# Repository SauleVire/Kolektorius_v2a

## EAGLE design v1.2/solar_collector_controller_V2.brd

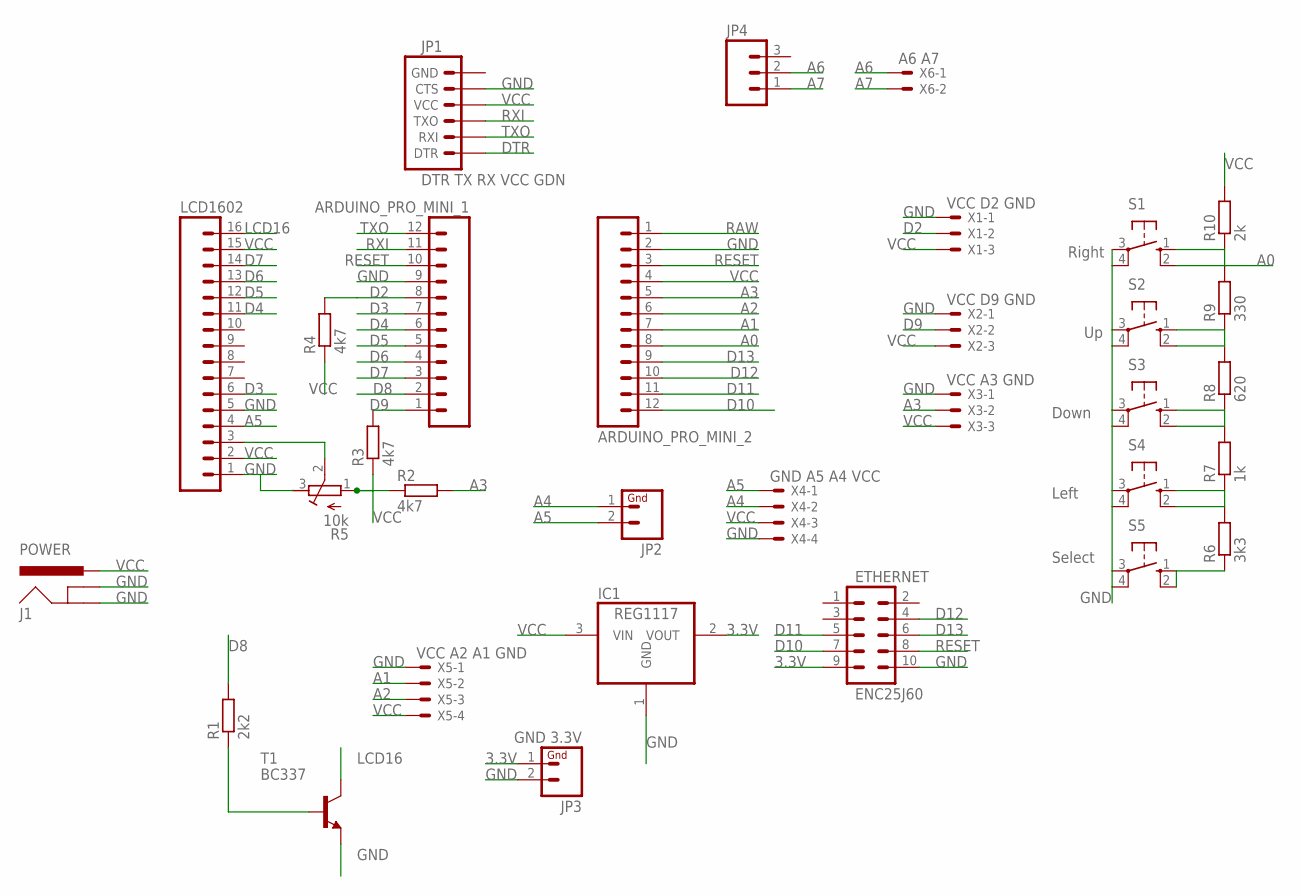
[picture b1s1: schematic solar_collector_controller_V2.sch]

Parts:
ARDUINO_PRO_MINI_1, ARDUINO_PRO_MINI_2: M12PTH; 1X12
ETHERNET: ENC25J60; AVR_ICSP
IC1: REG1117; SOT223
J1: POWER; POWER_JACK_PTH_LOCK
JP1: DTR TX RX VCC GDN; 1X06
JP2: M02PTH; 1X02
JP3: GND 3.3V; 1X02
JP4: M03PTH; 1X03
LCD1602: HEADER-16P-2.54; 16P-2.54
R1: 2k2; 0207/10
R2, R3, R4: 4k7; 0207/10
R5: 10k; RTRIM64W
R6: 3k3; 0207/10
R7: 1k; 0207/10
R8: 620; 0207/10
R9: 330; 0207/10
R10: 2k; 0207/10
S1: Right; B3F-10XX
S2: Up; B3F-10XX
S3: Down; B3F-10XX
S4: Left; B3F-10XX
S5: Select; B3F-10XX
T1: BC337; TO92
X1: VCC D2 GND; 22-23-2031
X2: VCC D9 GND; 22-23-2031
X3: VCC A3 GND; 22-23-2031
X4: GND A5 A4 VCC; 22-23-2041
X5: VCC A2 A1 GND; 22-23-2041
X6: A6 A7; 22-23-2021

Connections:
3.3V: ETHERNET.9, IC1.2 (VOUT), JP3.1
A0: ARDUINO_PRO_MINI_2.8, R9.2, R10.1, S1.1 (S), S1.2 (S1)
A1: ARDUINO_PRO_MINI_2.7, X5.2
A2: ARDUINO_PRO_MINI_2.6, X5.3
A3: ARDUINO_PRO_MINI_2.5, R2.2, X3.2
A4: JP2.1, X4.2
A5: JP2.2, LCD1602.4, X4.1
A6: JP4.2, X6.1
A7: JP4.1, X6.2
D2: ARDUINO_PRO_MINI_1.8, R4.2, X1.2
D3: ARDUINO_PRO_MINI_1.7, LCD1602.6
D4: ARDUINO_PRO_MINI_1.6, LCD1602.11
D5: ARDUINO_PRO_MINI_1.5, LCD1602.12
D6: ARDUINO_PRO_MINI_1.4, LCD1602.13
D7: ARDUINO_PRO_MINI_1.3, LCD1602.14
D8: ARDUINO_PRO_MINI_1.2, R1.2
D9: ARDUINO_PRO_MINI_1.1, R3.2, X2.2
D10: ARDUINO_PRO_MINI_2.12, ETHERNET.7
D11: ARDUINO_PRO_MINI_2.11, ETHERNET.5
D12: ARDUINO_PRO_MINI_2.10, ETHERNET.4
D13: ARDUINO_PRO_MINI_2.9, ETHERNET.6
DTR: JP1.1 (DTR)
GND: ARDUINO_PRO_MINI_1.9, ARDUINO_PRO_MINI_2.2, ETHERNET.10, IC1.1 (GND), J1.GND, J1.GNDBREAK, JP1.5 (CTS), JP3.2, LCD1602.1, LCD1602.5, R5.3 (A), S1.3, S1.4 (P1), S2.3, S2.4 (P1), S3.3, S3.4 (P1), S4.3, S4.4 (P1), S5.3, S5.4 (P1), T1.1 (E), X1.1, X2.1, X3.1, X4.4, X5.1
LCD16: LCD1602.16, T1.3 (C)
unnamed: LCD1602.3, R5.2 (S)
unnamed: R1.1, T1.2 (B)
unnamed: R6.1, S5.1 (S), S5.2 (S1)
unnamed: R6.2, R7.1, S4.1 (S), S4.2 (S1)
unnamed: R7.2, R8.1, S3.1 (S), S3.2 (S1)
unnamed: R8.2, R9.1, S2.1 (S), S2.2 (S1)
RAW: ARDUINO_PRO_MINI_2.1
RESET: ARDUINO_PRO_MINI_1.10, ARDUINO_PRO_MINI_2.3, ETHERNET.8
RXI: ARDUINO_PRO_MINI_1.11, JP1.3 (TXO)
TXO: ARDUINO_PRO_MINI_1.12, JP1.2 (RXI)
VCC: ARDUINO_PRO_MINI_2.4, IC1.3 (VIN), J1.PWR, JP1.4 (VCC), LCD1602.2, LCD1602.15, R2.1, R3.1, R4.1, R5.1 (E), R10.2, X1.3, X2.3, X3.3, X4.3, X5.4

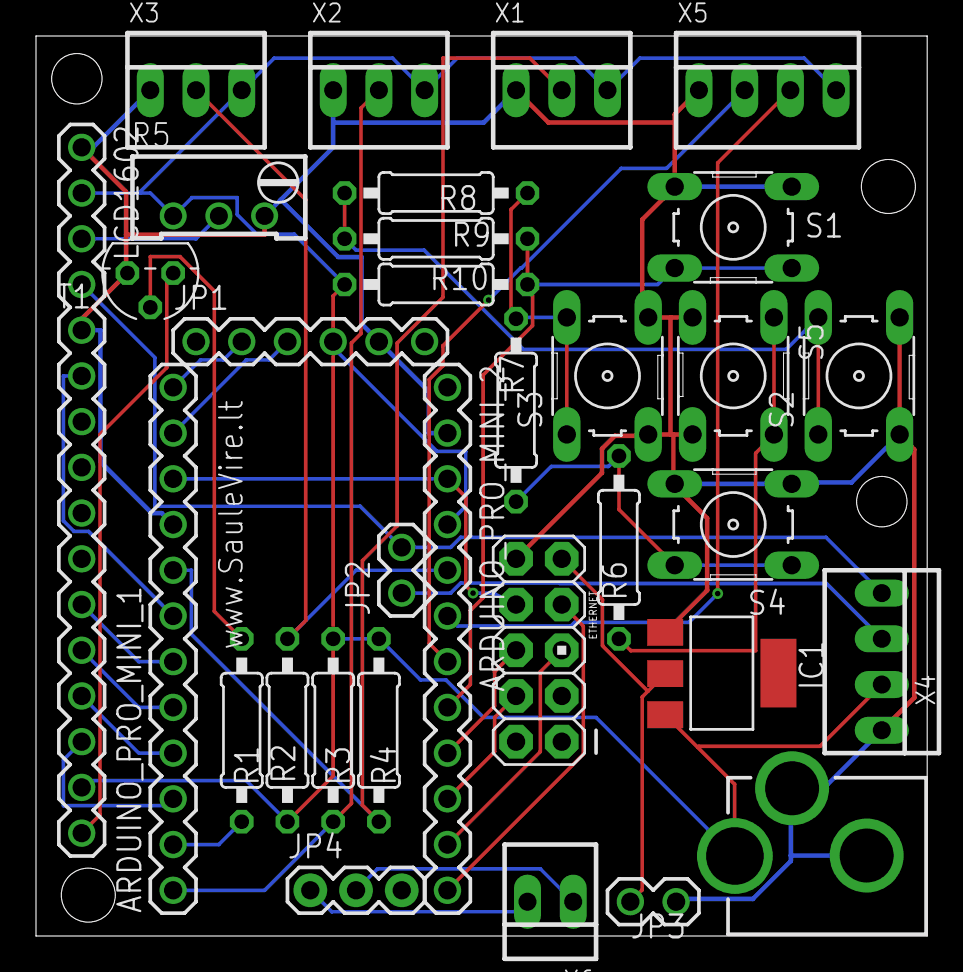
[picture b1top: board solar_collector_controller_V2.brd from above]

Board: 2 copper layers, 49.5 x 50.0 mm, 32 parts (0 on the bottom side), 33 nets.

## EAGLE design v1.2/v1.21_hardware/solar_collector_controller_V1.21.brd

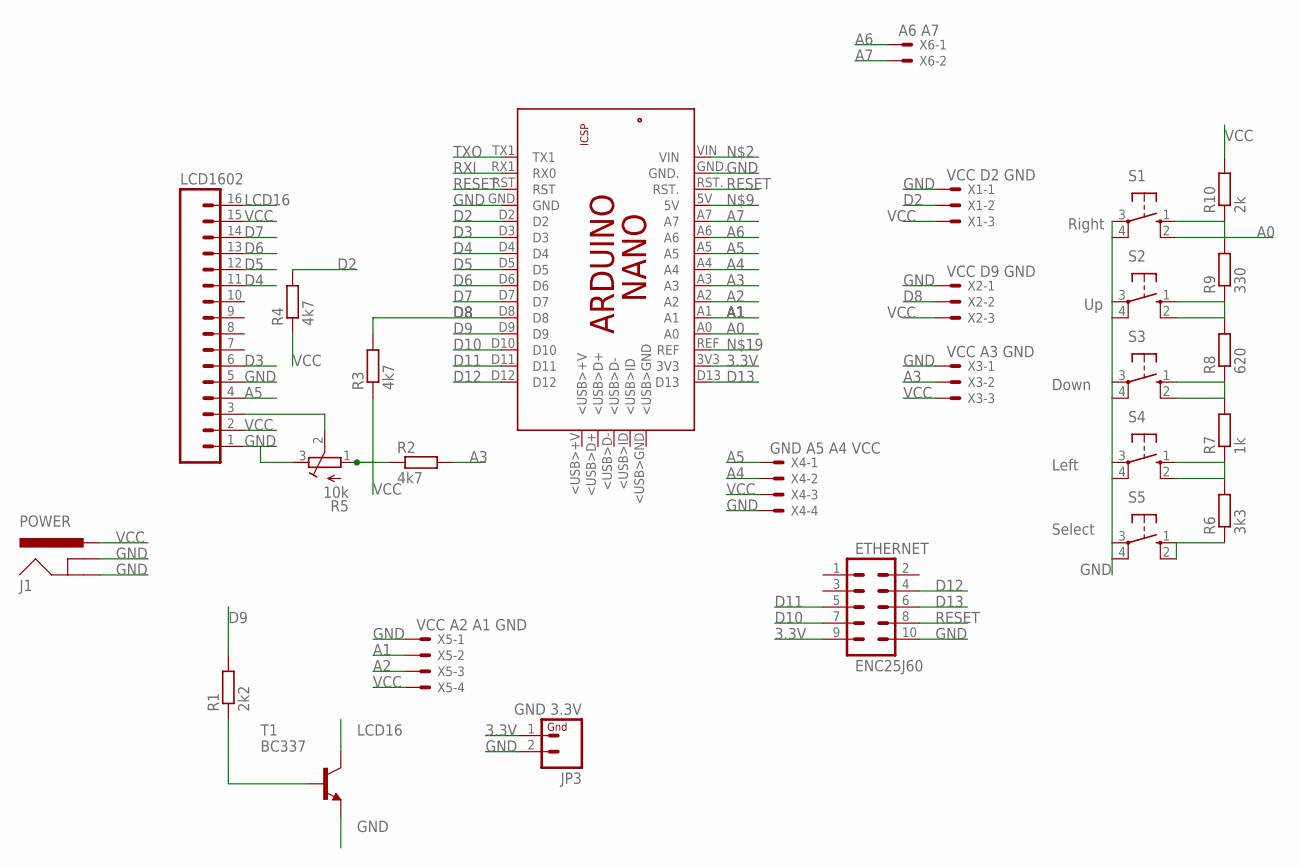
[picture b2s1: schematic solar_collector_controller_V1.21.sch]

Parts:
ETHERNET: ENC25J60; AVR_ICSP
J1: POWER; POWER_JACK_PTH_LOCK
JP3: GND 3.3V; 1X02
LCD1602: HEADER-16P-2.54; 16P-2.54
PCB1: ARDUINO_NANO
R1: 2k2; 0207/10
R2, R3, R4: 4k7; 0207/10
R5: 10k; RTRIM64W
R6: 3k3; 0207/10
R7: 1k; 0207/10
R8: 620; 0207/10
R9: 330; 0207/10
R10: 2k; 0207/10
S1: Right; B3F-10XX
S2: Up; B3F-10XX
S3: Down; B3F-10XX
S4: Left; B3F-10XX
S5: Select; B3F-10XX
T1: BC337; TO92
X1: VCC D2 GND; 22-23-2031
X2: VCC D9 GND; 22-23-2031
X3: VCC A3 GND; 22-23-2031
X4: GND A5 A4 VCC; 22-23-2041
X5: VCC A2 A1 GND; 22-23-2041
X6: A6 A7; 22-23-2021

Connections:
3.3V: ETHERNET.9, JP3.1, PCB1.3V3
A0: PCB1.A0, R9.2, R10.1, S1.1 (S), S1.2 (S1)
A1: PCB1.A1, X5.2
A2: PCB1.A2, X5.3
A3: PCB1.A3, R2.2, X3.2
A4: PCB1.A4, X4.2
A5: LCD1602.4, PCB1.A5, X4.1
A6: PCB1.A6, X6.1
A7: PCB1.A7, X6.2
D2: PCB1.D2, R4.2, X1.2
D3: LCD1602.6, PCB1.D3
D4: LCD1602.11, PCB1.D4
D5: LCD1602.12, PCB1.D5
D6: LCD1602.13, PCB1.D6
D7: LCD1602.14, PCB1.D7
D8: PCB1.D8, R3.2, X2.2
D9: PCB1.D9, R1.2
D10: ETHERNET.7, PCB1.D10
D11: ETHERNET.5, PCB1.D11
D12: ETHERNET.4, PCB1.D12
D13: ETHERNET.6, PCB1.D13
GND: ETHERNET.10, J1.GND, J1.GNDBREAK, JP3.2, LCD1602.1, LCD1602.5, PCB1.GND, PCB1.GND., R5.3 (A), S1.3, S1.4 (P1), S2.3, S2.4 (P1), S3.3, S3.4 (P1), S4.3, S4.4 (P1), S5.3, S5.4 (P1), T1.1 (E), X1.1, X2.1, X3.1, X4.4, X5.1
LCD16: LCD1602.16, T1.3 (C)
unnamed: LCD1602.3, R5.2 (S)
unnamed: R1.1, T1.2 (B)
unnamed: R6.1, S5.1 (S), S5.2 (S1)
unnamed: R6.2, R7.1, S4.1 (S), S4.2 (S1)
unnamed: R7.2, R8.1, S3.1 (S), S3.2 (S1)
unnamed: R8.2, R9.1, S2.1 (S), S2.2 (S1)
RESET: ETHERNET.8, PCB1.RST, PCB1.RST.
RXI: PCB1.RX1 (RX0)
TXO: PCB1.TX1
VCC: J1.PWR, LCD1602.2, LCD1602.15, R2.1, R3.1, R4.1, R5.1 (E), R10.2, X1.3, X2.3, X3.3, X4.3, X5.4

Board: 2 copper layers, 27 parts (0 on the bottom side), 31 nets, no tracks yet.

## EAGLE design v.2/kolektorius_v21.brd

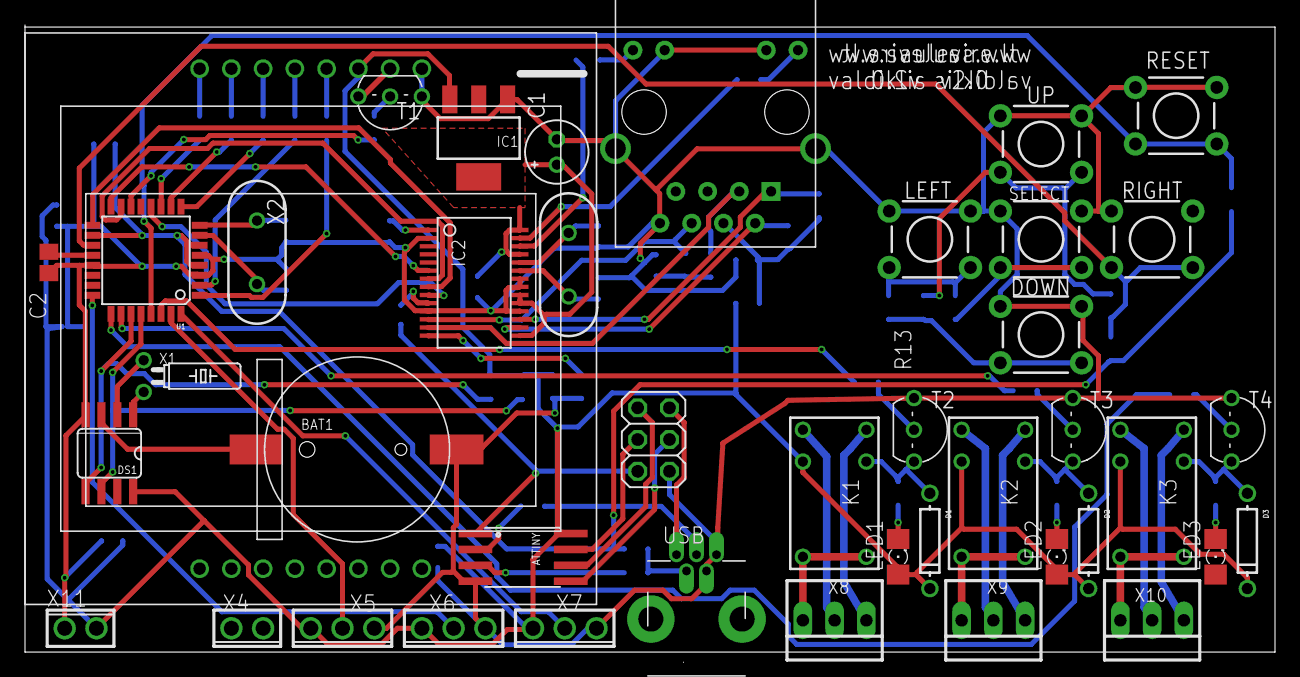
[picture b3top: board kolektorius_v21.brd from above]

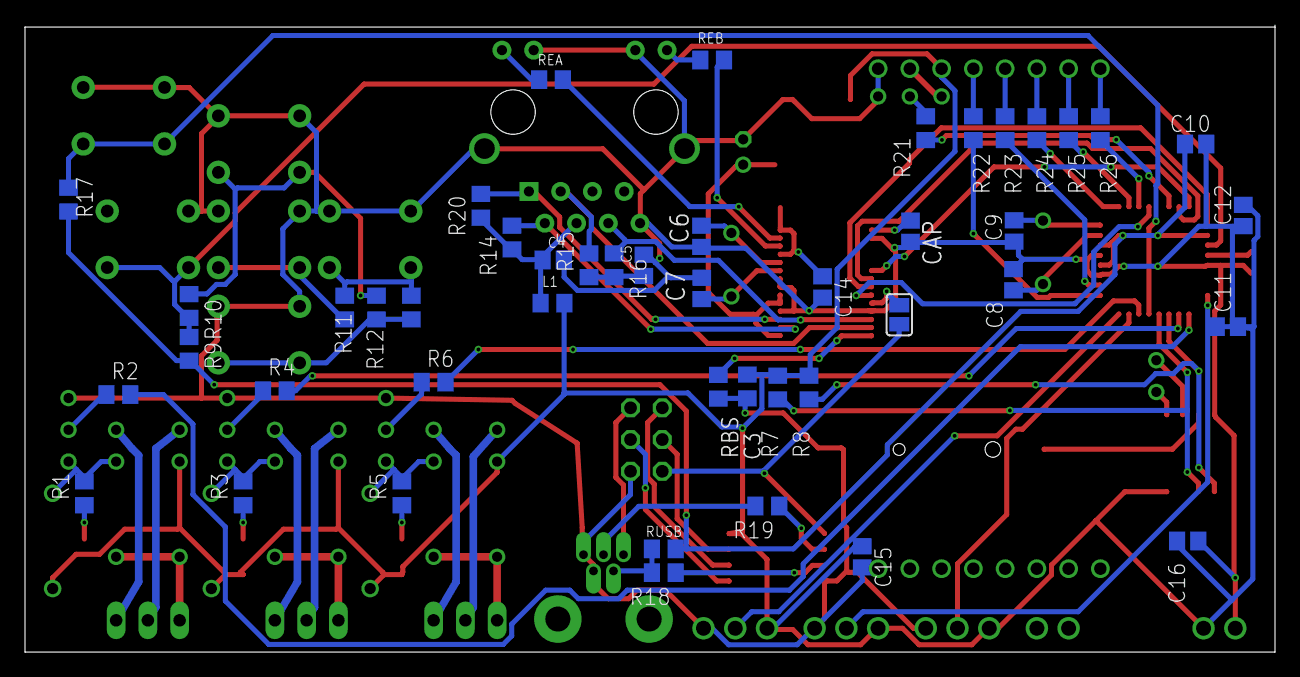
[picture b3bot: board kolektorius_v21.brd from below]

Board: 2 copper layers, 100.0 x 50.2 mm, 88 parts (46 on the bottom side), 83 nets.

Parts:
ATTINY: ATTINY45SO8S2; SO8S2
BAT1: BATTCON_12MM_SMT
C1: 100u; E2-5
C2, C10, C11, C12, C14, C15, C16: 100n; C0805
C3: 0.1u; C0805
C4, C5: 0.1µ; C0805
C6, C7: 18p; C0805
C8, C9: 22p; C0805
CAP: 10u; C0805
D1, D2, D3: DO-1N4148
DOWN: TACTILE-PTH
DS1: DS1307; SO08
IC1: LM1117-33; SOT223
IC2: ENC28J60; SSOP28DB
ISP: 2X03
K1, K2, K3: G5V1
L1: Bead; R0805
LED1, LED2, LED3: 1206
LEFT: TACTILE-PTH
R1, R3, R5: 470; R0805
R2, R4, R6, R11: 3k3; R0805
R7, R8, R17, R22, R23, R24, R25, R26: 10k; R0805
R9: 2k; R0805
R10: 330; R0805
R12: 620; R0805
R13, R21: 1k; R0805
R14, R15, R16, R20: 49; R0805
R18, R19: 47; R0805
RBS: 2.32K; R0805
REA: 330; R0805
REB: 330; R0805
RESET: TACTILE-PTH
RIGHT: TACTILE-PTH
RJ1: HR911105A
RUSB: 1.5k; R0805
SELECT: TACTILE-PTH
SJ1: SJ
T1, T2, T3, T4: 2N2222; TO92-EBC-OVAL
U1: ATMEGA328P; TQFP32-08
U$1: CELLPHONE_NOKIA_5100; CELLPHONE_NOKIA_5100_SPARKFUN
UP: TACTILE-PTH
USB: USB-MINIB-THM-MOLEX
X1: 32.768kHz; TC26H
X2: 16MHz; HC49US
X3: 25MHz; HC49US
X4, X11: 2POL254
X5, X6, X7: 3POL254
X8, X9, X10: 22-23-2031

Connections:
+3V3: C1.+, C14.1, IC1.4, IC2.15, IC2.19, IC2.20, IC2.25, IC2.28
+5V: ATTINY.8, C3.1, C11.2, C12.2, C15.1, C16.1, D1.C, D2.C, D3.C, DS1.8, IC1.3, K1.2, K2.2, K3.2, L1.2, LED1.A, LED2.A, R7.2, R8.2, U$1.P$6, X5.3, X6.3, X7.3, X11.2
A1: U1.24, X6.2
A2: R2.2, U1.25
A3: R4.2, U1.26
A6: R9.1, R10.2, RIGHT.3, RIGHT.4, U1.19
D0: R6.2, U1.30
D1: U1.31, X5.2
D2: U1.32, X7.2
D3: R22.2, U1.1
D4: R23.2, U1.2
D5: R24.2, U1.9
D6: R25.2, U1.10
D7: R26.2, U1.11
D8: IC2.9, U1.12
D10: R21.2, U1.14
D11: IC2.7, U1.15
D12: IC2.6, U1.16
D13: IC2.8, U1.17
D+: ATTINY.2, R19.1
D-: ATTINY.3, R18.1
GND: ATTINY.4, BAT1.P$1, C1.-, C2.2, C3.2, C4.1, C5.1, C6.2, C7.2, C8.1, C9.1, C10.2, C11.1, C12.1, C14.2, C15.2, C16.2, CAP.2, DOWN.1, DOWN.2, DS1.4, IC1.1, IC2.2, IC2.11, IC2.18, IC2.21, IC2.22, ISP.6, LEFT.1, LEFT.2, RBS.1, RESET.1, RESET.2, RIGHT.1, RJ1.G-, RJ1.GND, RJ1.SHIELD0, RJ1.SHIELD1, RJ1.Y-, SELECT.1, SELECT.2, T1.E, T2.E, T3.E, T4.E, U1.3, U1.5, U1.21, U$1.P$8, UP.1, UP.2, USB.GND, USB.ID, X5.1, X6.1, X7.1, X11.1
LEDA: REA.2, RJ1.G+
LEDB: REB.2, RJ1.Y+
MISO: ATTINY.6, ISP.1
MOSI: ATTINY.5, ISP.4
unnamed: LEFT.3, LEFT.4, R11.2, R13.1
unnamed: D2.A, K2.9, R3.2, T3.C
unnamed: R4.1, T3.B
unnamed: K2.5, K2.6, X9.3
unnamed: K2.1, X9.2
unnamed: DOWN.3, DOWN.4, R12.1, R13.2
unnamed: LED2.C, R3.1
unnamed: DS1.1, X1.2
unnamed: R10.1, R12.2, UP.3, UP.4
unnamed: D1.A, K1.9, R5.2, T2.C
unnamed: D3.A, K3.9, R1.2, T4.C
unnamed: R2.1, T4.B
unnamed: K2.10, X9.1
unnamed: K1.10, X8.1
unnamed: K3.10, X10.1
unnamed: R6.1, T2.B
unnamed: R11.1, SELECT.3, SELECT.4
unnamed: K3.5, K3.6, X10.3
unnamed: K3.1, X10.2
unnamed: LED3.C, R1.1
unnamed: R22.1, U$1.P$5
unnamed: R25.1, U$1.P$2
unnamed: R24.1, U$1.P$3
unnamed: R23.1, U$1.P$4
unnamed: T1.C, U$1.P$7
unnamed: K1.5, K1.6, X8.3
unnamed: K1.1, X8.2
unnamed: DS1.2, X1.1
unnamed: LED1.C, R5.1
unnamed: C9.2, U1.8, X2.1
unnamed: C8.2, U1.7, X2.2
unnamed: IC2.27, REA.1
unnamed: C2.1, U1.20
unnamed: BAT1.P$2, DS1.3
unnamed: IC2.26, REB.1
unnamed: R19.2, USB.D+
unnamed: CAP.1, IC2.1
unnamed: C6.1, IC2.24, X3.2
unnamed: C7.1, IC2.23, X3.1
unnamed: R21.1, T1.B
unnamed: R18.2, RUSB.1, USB.D-
unnamed: R17.1, RESET.3, RESET.4, U1.29
unnamed: ATTINY.1, ISP.5, SJ1.1
unnamed: C5.2, R15.1, R16.2
unnamed: IC2.14, RBS.2
RD+: IC2.13, R15.2, RJ1.RD+
RD-: IC2.12, R16.1, RJ1.RD-
RESET: IC2.10, SJ1.2
SCK: ATTINY.7, ISP.3
SCL: DS1.6, R7.1, U1.28
SDA: DS1.5, R8.1, U1.27
TCT: C4.2, L1.1, R14.2, R20.1, RJ1.P4
TD+: IC2.17, R20.2, RJ1.TD+
TD-: IC2.16, R14.1, RJ1.TD-
V$: R26.1, U$1.P$1
VCC: C10.1, R9.2, R17.2, RUSB.2, U1.4, U1.6, U1.18
VIN: ISP.2, USB.VBUS

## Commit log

2014-10-27 :lollipop: Added .gitattributes & .gitignore files
2014-10-27 arduino nano ch340
2014-10-30 pataisymai
2014-10-30 versija 1.21

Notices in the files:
parts and their libraries:
SparkFun-DigitalIC: Licensing: CC v3.0 Share-Alike You are welcome to use this library for commercial purposes.
